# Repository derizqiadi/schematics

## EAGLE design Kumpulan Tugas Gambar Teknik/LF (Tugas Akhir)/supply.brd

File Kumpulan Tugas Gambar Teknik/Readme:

Hello!
My name is Derizqiadi Thoriq, student of Yogyakarta State University Gunung Kidul campus.
My NIM is 21507224030 and from GK1 class.

This repository was created to place the assignments that i was made while i was studying in the "Gambar Teknik" course in Semester 1.
This repository including :

1. Schematics assignment where i compile the components in the eagle application in schematic (.sch) form.
2. KMMI assignment where i arrange components in "board" (.brd) form and connect between components so that they can be used.
3. LF (Tugas Akhir) assignment where i arrange the components that have been provided. After that i connected the components on the coard (.brd) file, so that the components can be used.
4. Tugas Komponen, where i put the task that has been given previously ( tugas komponen, dan tugas adc_with_LDR).

Thank you for viewing my github repository page, i hope that what i upload on this page can be useful for other people, and i also hope to add more files to my repository and increase my skill in "Gambar Teknik" course.

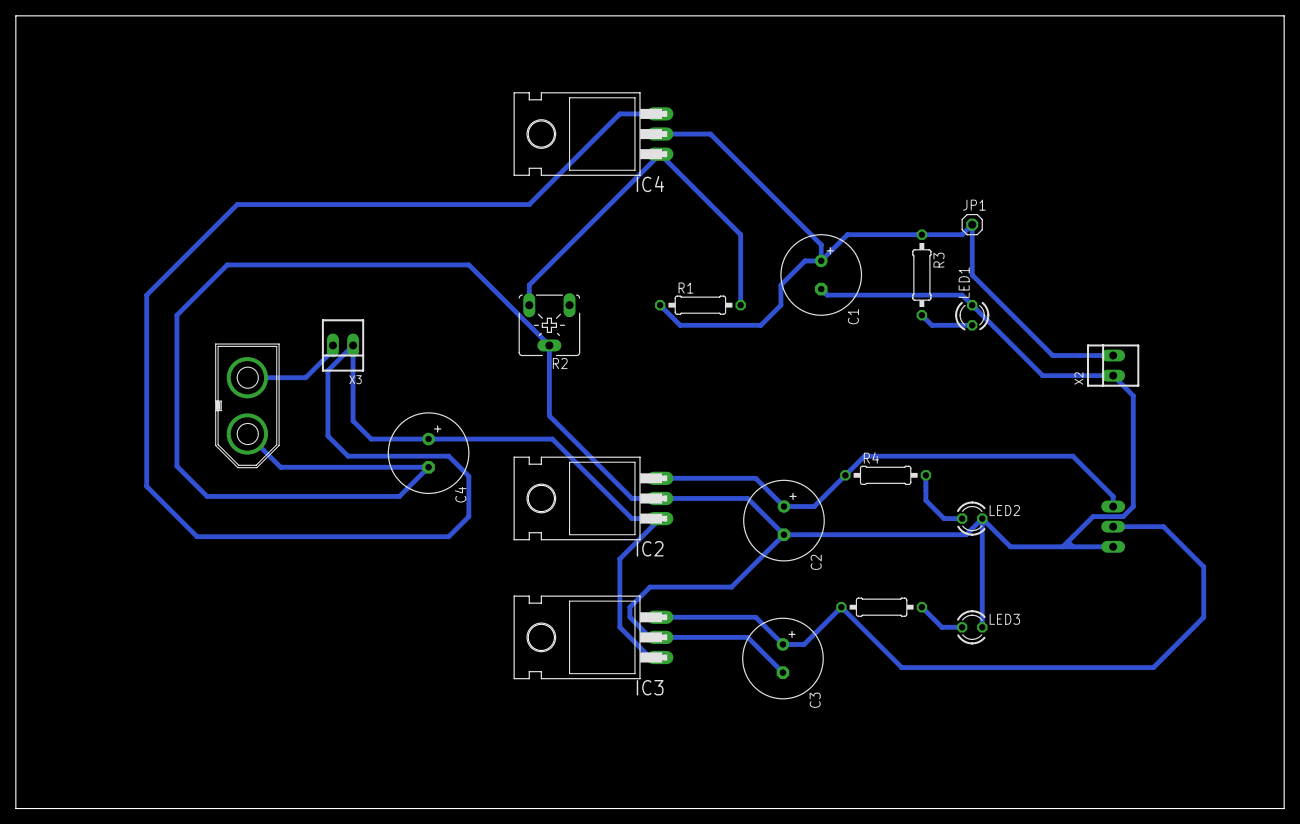
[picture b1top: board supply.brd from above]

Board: 2 copper layers, 160.0 x 100.0 mm, 20 parts (1 on the bottom side), 10 nets.

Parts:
C1, C2, C3, C4: 1000uF/16V; E3,5-10
IC2, IC3: 7805T; TO220H
IC4: 317T; TO220H
JP1: 1X01
LED1, LED2, LED3: LED3MM
R1: 1K2; 0207/10
R2: 20K; CA6V
R3, R4, R5: 1K; 0207/10
VIN: CON-XT60M
X1: VSYS; 22-23-2031
X2: VMOT; 22-23-2021
X3: switch; 22-23-2021

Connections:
+12V: C3.+, IC3.3, R5.1, X1.2
GND: C1.-, C2.-, C3.-, C4.-, IC2.2, IC3.2, LED1.K, LED2.K, LED3.K, R2.S, VIN.V-, X1.3, X2.1
unnamed: IC4.1, R1.2, R2.E
unnamed: LED1.A, R3.2
unnamed: LED3.A, R5.2
unnamed: VIN.V+, X3.2
unnamed: LED2.A, R4.2
VCC: C2.+, IC2.3, R4.1, X1.1
VDD: C1.+, IC4.2, JP1.1, R1.1, R3.1, X2.2
VPP: C4.+, IC2.1, IC3.1, IC4.3, X3.1

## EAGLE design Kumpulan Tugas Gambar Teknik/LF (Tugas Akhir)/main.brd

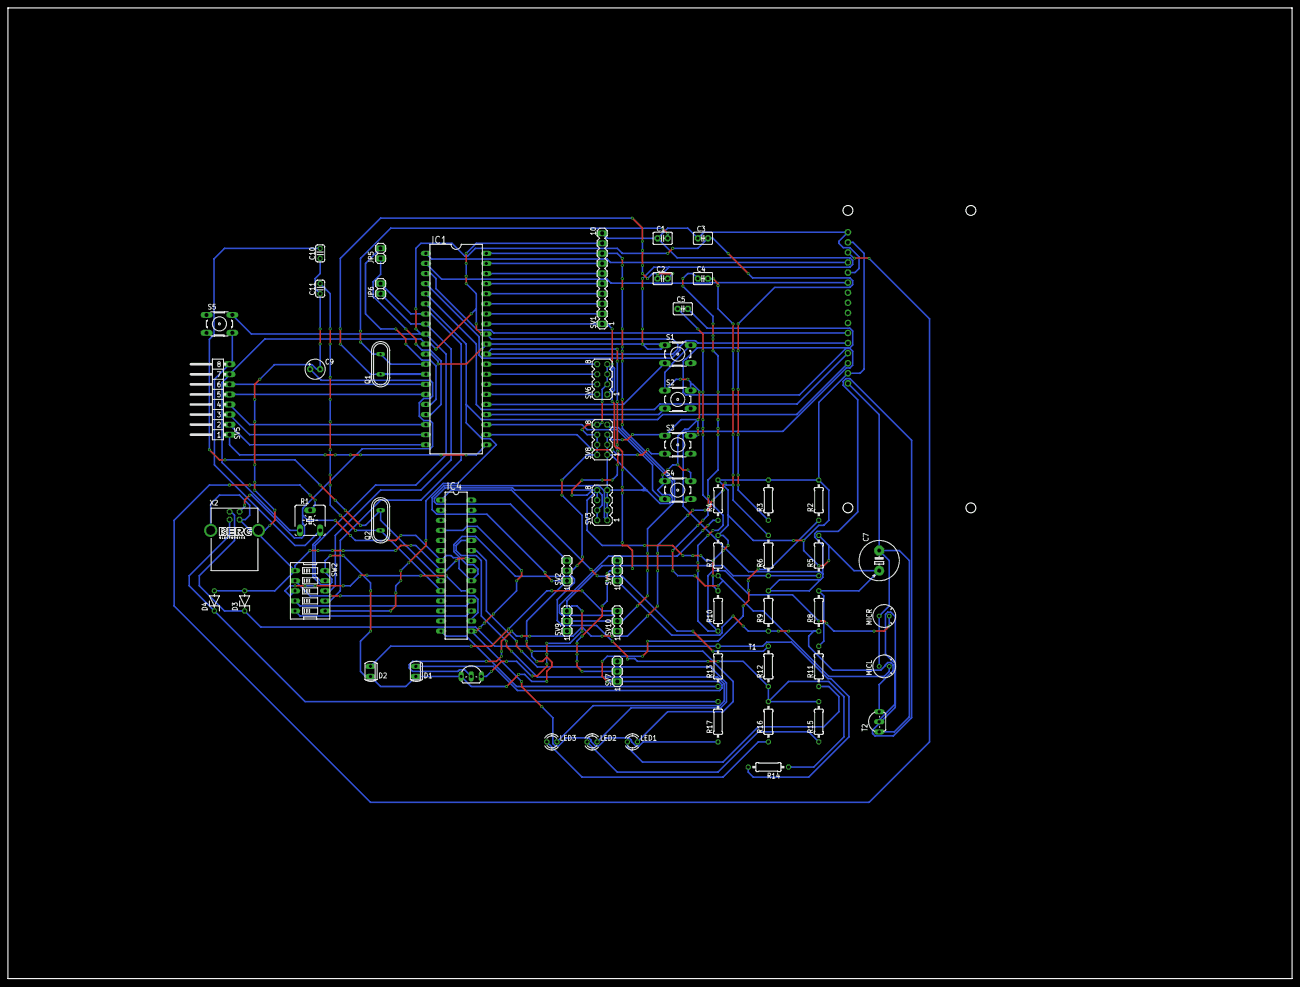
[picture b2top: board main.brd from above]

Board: 2 copper layers, 323.8 x 244.8 mm, 61 parts (1 on the bottom side), 65 nets.

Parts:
C1, C2: 22p; C2.5-3
C3: 10nF; C2.5-3
C4, C5: 100nF; C2.5-3
C7: 1000uF/16V; E5-10,5
C9: 10uF/16V; E2,5-5
C10, C11: 22pF; C025-024X044
D1, D2: SFH225
D3, D4: DZ3,6V; ZDIO-5
DIS1: TUXGR_16X2_R2
IC1: MEGA16-P; DIL40
IC4: MEGA8-P; DIL28-3
JP5, JP6: 1X02
LED1: merah; LED3MM
LED2: Merah; LED3MM
LED3: hijau; LED3MM
MICL: MC; F6050AP
MICR: MC; F6050AP
Q1: 8MHz; QS
Q2: 12MHz; QS
R1: 20K; CA6V
R2, R4: 56K; 0207/10
R3, R5, R7, R8, R10, R12: 10K; 0207/10
R6, R9: 100K; 0207/10
R11, R15, R16: 330; 0207/10
R13, R17: 68; 0207/10
R14: 2K2; 0207/10
S1, S2, S3, S4, S5: B3F-10XX
SV1: MA10-1
SV2, SV4, SV7, SV9, SV10: MA03-1
SV3, SV6, SV8: MA04-2
SV5: MA08-1W
SW2: EDG-05
T1, T2: TO92-EBC
X2: PN61729-S

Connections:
DGND: C9.-, C10.1, C11.1, D3.A, D4.A, IC4.8, IC4.22, SW2.1, X2.4, X2.S1, X2.S2
GND: C1.1, C2.1, C3.1, C7.-, D1.K, D2.K, DIS1.1, DIS1.5, DIS1.16, IC1.11, IC1.31, LED1.K, MICL.1, MICR.1, R1.E, S1.1, S1.2, S2.1, S2.2, S3.1, S3.2, S4.1, S4.2, S5.3, S5.4, SV1.10, SV2.1, SV3.1, SV3.3, SV3.5, SV3.7, SV5.8, SV8.1, SV8.3, SV8.5, SV8.7, SW2.10, T1.E, T2.E
MISO: IC1.7, JP6.2, SW2.7
MOSI: DIS1.14, IC1.6, SW2.6
unnamed: IC1.33, SV1.1, SV4.2, SV7.2
unnamed: IC1.34, SV1.2
unnamed: IC1.35, SV1.3
unnamed: IC1.36, SV1.4
unnamed: IC1.37, SV1.5
unnamed: IC1.38, SV1.6
unnamed: IC1.39, SV1.7
unnamed: D2.A, R4.1, SV10.3
unnamed: IC1.24, S2.3, S2.4
unnamed: DIS1.13, IC1.5
unnamed: DIS1.12, IC1.4
unnamed: DIS1.11, IC1.3
unnamed: DIS1.6, IC1.2
unnamed: R5.1, R6.1, SV9.3, T1.C
unnamed: DIS1.3, R1.S
unnamed: C1.2, IC1.12, Q1.2
unnamed: C2.2, IC1.13, Q1.1
unnamed: DIS1.4, IC1.1
unnamed: D1.A, R2.1, SV7.1
unnamed: IC1.23, S4.3, S4.4
unnamed: IC1.40, SV1.8, SV9.2, SV10.2
unnamed: C4.2, R6.2, T1.B
unnamed: C4.1, MICL.2, R7.1
unnamed: R8.1, R9.1, SV4.1, T2.C
unnamed: C5.2, R9.2, T2.B
unnamed: C5.1, MICR.2, R10.1
unnamed: IC1.22, S3.3, S3.4
unnamed: IC1.25, S1.3, S1.4
unnamed: IC1.21, SV5.1
unnamed: IC1.20, SV5.2
unnamed: IC1.19, SV5.3
unnamed: IC1.18, SV5.4
unnamed: IC1.15, SV5.5
unnamed: IC1.14, SV5.6
unnamed: IC1.16, JP5.2
unnamed: IC1.17, JP5.1
unnamed: LED1.A, R11.1
unnamed: IC4.1, R12.2
unnamed: IC1.26, SV6.2
unnamed: IC1.27, SV6.4
unnamed: IC1.28, SV6.6
unnamed: IC1.29, SV6.8
unnamed: C10.2, IC4.9, Q2.2
unnamed: C11.2, IC4.10, Q2.1
unnamed: IC4.14, R13.1
unnamed: LED2.A, R15.1
unnamed: LED3.A, R16.1
unnamed: IC4.23, LED2.K
unnamed: IC4.24, LED3.K
unnamed: D4.C, R17.2, X2.3
unnamed: IC4.4, IC4.15, R17.1
unnamed: D3.C, R13.2, R14.2, X2.2
unnamed: IC4.17, SW2.5
unnamed: IC4.18, SW2.4
unnamed: IC4.19, SW2.3
unnamed: IC4.16, SW2.2
RESET: C3.2, IC1.9, R3.1, S5.1, S5.2, SW2.9
SCK: IC1.8, JP6.1, SW2.8
VCC: C7.+, DIS1.2, DIS1.15, IC1.10, IC1.30, IC1.32, R1.A, R2.2, R3.2, R4.2, R5.2, R7.2, R8.2, R10.2, R11.2, SV1.9, SV2.3, SV3.2, SV3.4, SV3.6, SV3.8, SV5.7
VDD: SV2.2, SV6.1, SV6.3, SV6.5, SV6.7, SV8.2, SV8.4, SV8.6, SV8.8
VPP: C9.+, IC4.7, IC4.20, R12.1, R14.1, R15.2, R16.2, X2.1

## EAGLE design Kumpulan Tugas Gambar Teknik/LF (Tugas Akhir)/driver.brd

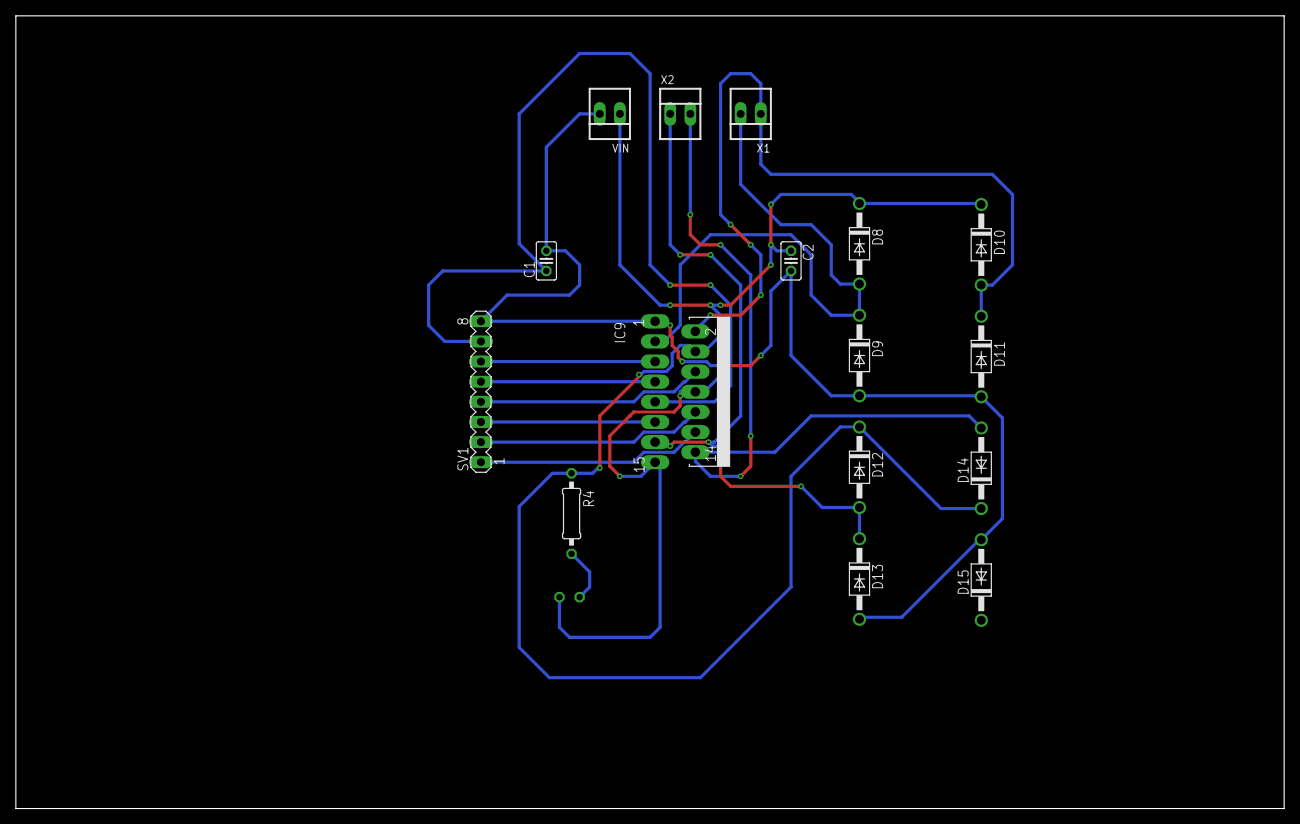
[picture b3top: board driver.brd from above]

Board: 2 copper layers, 160.0 x 100.0 mm, 17 parts (1 on the bottom side), 14 nets.

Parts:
C1, C2: 100nF; C025-025X050
D8, D9, D10, D11, D12, D13, D14, D15: 1N4004; DO41-10
IC9: L298; MULTIWATT-15
LED1: LED3MM
R4: 330; 0207/10
SV1: MA08-1
VIN: 22-23-2021
X1, X2: 22-23-2021

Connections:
GND: C1.2, C2.2, D9.A, D11.A, D13.A, D15.A, IC9.1, IC9.8, IC9.15, LED1.K, SV1.8, VIN.2
unnamed: IC9.5, SV1.6
unnamed: IC9.7, SV1.5
unnamed: IC9.12, SV1.1
unnamed: IC9.10, SV1.2
unnamed: IC9.6, SV1.4
unnamed: IC9.11, SV1.3
unnamed: LED1.A, R4.2
unnamed: D8.A, D9.C, IC9.3, X1.2
unnamed: D10.A, D11.C, IC9.2, X1.1
unnamed: D12.A, D13.C, IC9.13, X2.1
unnamed: D14.A, D15.C, IC9.14, X2.2
VCC: C1.1, IC9.9, SV1.7
VDD: C2.1, D8.C, D10.C, D12.C, D14.C, IC9.4, R4.1, VIN.1

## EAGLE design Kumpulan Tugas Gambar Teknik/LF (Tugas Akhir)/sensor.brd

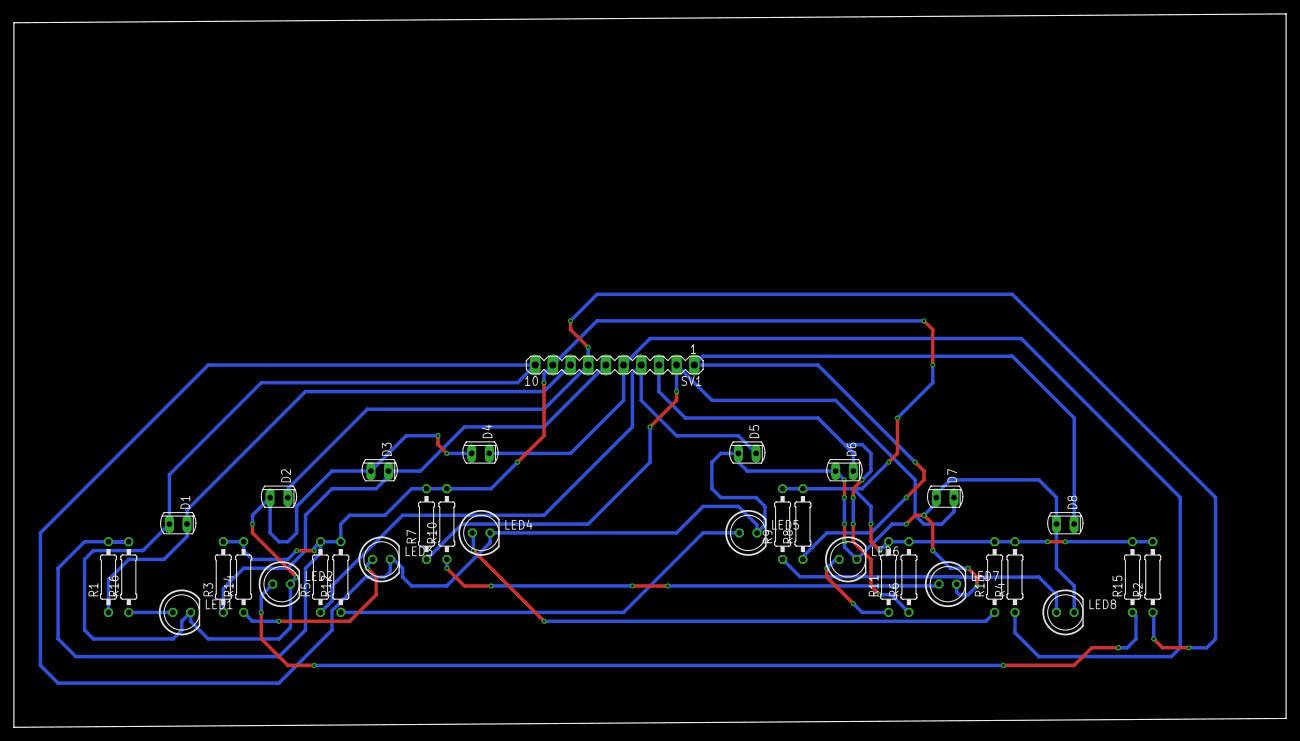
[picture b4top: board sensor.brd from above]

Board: 2 copper layers, 182.9 x 102.5 mm, 33 parts (0 on the bottom side), 18 nets.

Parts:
D1, D2, D3, D4, D5, D6, D7, D8: PhotoDioda; SFH225
LED1, LED2, LED3, LED4, LED5, LED6, LED7, LED8: LED putih SB; LED5MM
R1, R2, R3, R4, R5, R6, R7, R8: 0207/10
R9, R10, R11, R12, R13, R14, R15, R16: 330; 0207/10
SV1: MA10-1

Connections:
GND: D1.A, D2.A, D3.A, D4.A, D5.A, D6.A, D7.A, D8.A, LED1.K, LED2.K, LED3.K, LED4.K, LED5.K, LED6.K, LED7.K, LED8.K, SV1.10
unnamed: LED7.A, R10.1
unnamed: D7.K, R7.1, SV1.2
unnamed: D8.K, R8.1, SV1.1
unnamed: D1.K, R1.1, SV1.8
unnamed: D2.K, R2.1, SV1.7
unnamed: D3.K, R3.1, SV1.6
unnamed: D5.K, R5.1, SV1.4
unnamed: D4.K, R4.1, SV1.5
unnamed: D6.K, R6.1, SV1.3
unnamed: LED6.A, R11.1
unnamed: LED5.A, R12.1
unnamed: LED4.A, R13.1
unnamed: LED3.A, R14.1
unnamed: LED2.A, R15.1
unnamed: LED1.A, R16.1
unnamed: LED8.A, R9.1
VCC: R1.2, R2.2, R3.2, R4.2, R5.2, R6.2, R7.2, R8.2, R9.2, R10.2, R11.2, R12.2, R13.2, R14.2, R15.2, R16.2, SV1.9

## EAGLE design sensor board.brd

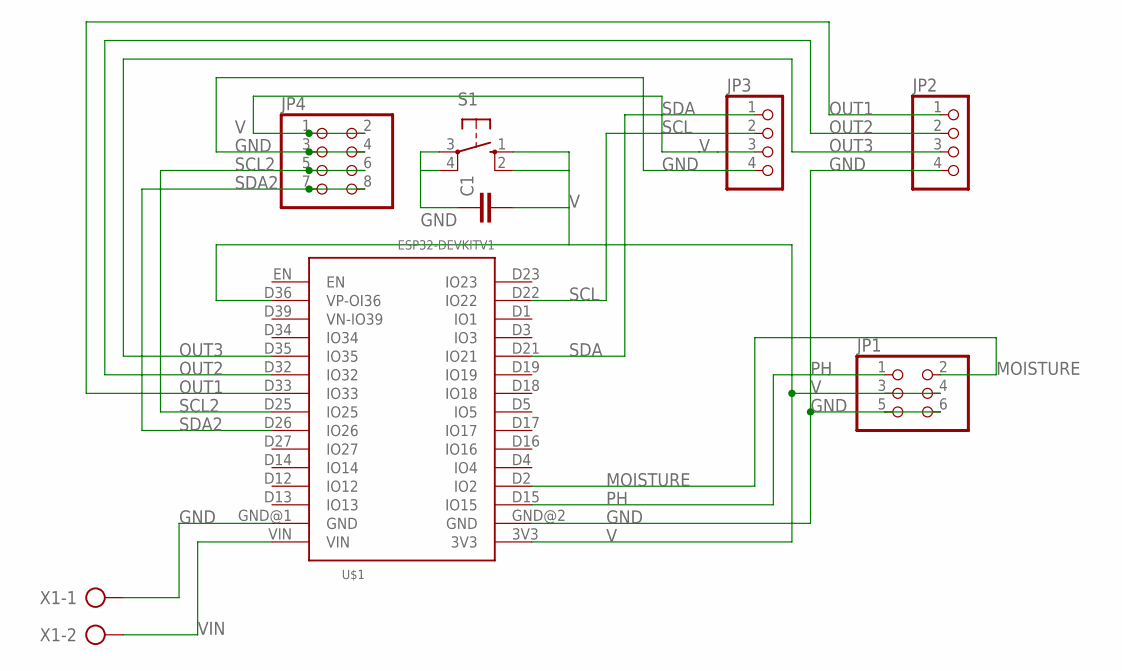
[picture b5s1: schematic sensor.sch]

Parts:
C1: C-EU050-030X075; C050-030X075
JP1: PINHD-2X3; 2X03
JP2, JP3: PINHD-1X4; 1X04
JP4: PINHD-2X4; 2X04
S1: 10-XX; B3F-10XX
U$1: ESP32DEVKITV1; ESP32-DEVKITV1
X1: AK300/2

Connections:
GND: C1.1, JP1.5, JP1.6, JP2.4, JP3.4, JP4.3, JP4.4, S1.3, S1.4 (P1), U$1.GND@1 (GND), U$1.GND@2 (GND), X1.1
MOISTURE: JP1.2, U$1.D2 (IO2)
OUT1: JP2.1, U$1.D33 (IO33)
OUT2: JP2.2, U$1.D32 (IO32)
OUT3: JP2.3, U$1.D35 (IO35)
PH: JP1.1, U$1.D15 (IO15)
SCL: JP3.2, U$1.D22 (IO22)
SCL2: JP4.5, JP4.6, U$1.D25 (IO25)
SDA: JP3.1, U$1.D21 (IO21)
SDA2: JP4.7, JP4.8, U$1.D26 (IO26)
V: C1.2, JP1.3, JP1.4, JP3.3, JP4.1, JP4.2, S1.1 (S), S1.2 (S1), U$1.3V3, U$1.D36 (VP-OI36)
VIN: U$1.VIN, X1.2

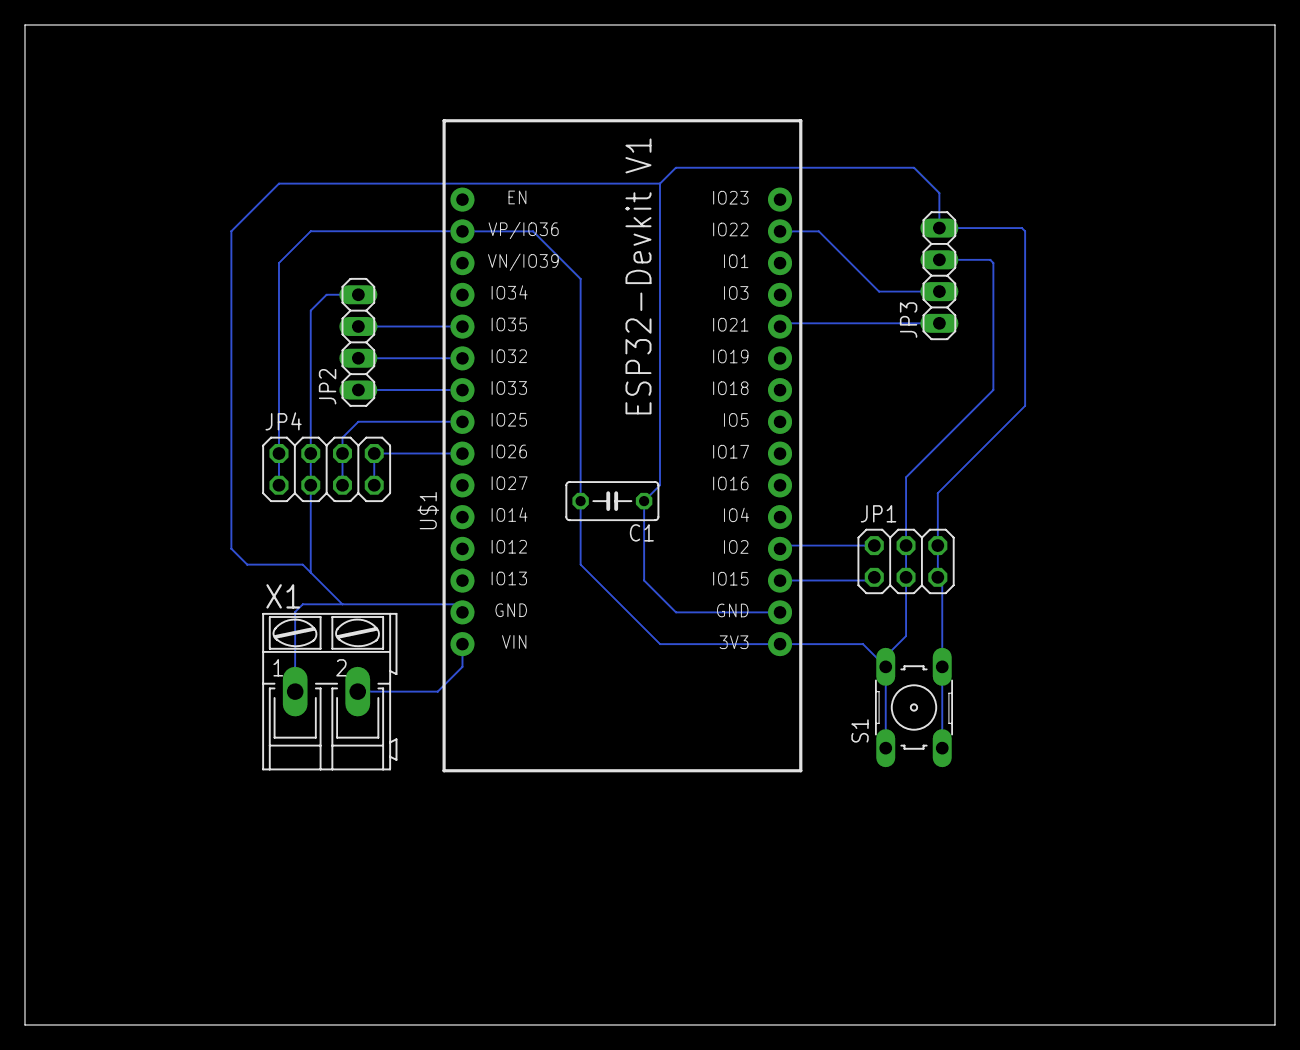
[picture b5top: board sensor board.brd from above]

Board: 2 copper layers, 100.0 x 80.0 mm, 8 parts (0 on the bottom side), 12 nets.

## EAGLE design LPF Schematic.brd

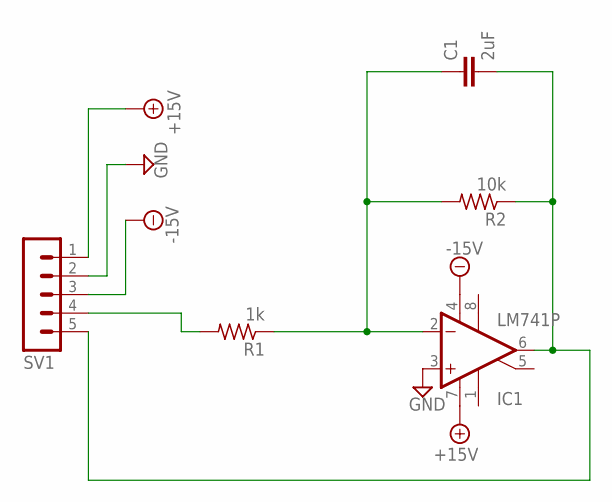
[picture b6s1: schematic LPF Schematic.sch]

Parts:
C1: 2uF; C0603
IC1: LM741P; DIL08
R1: 1k; R0603
R2: 10k; R0603
SV1: MA05-1

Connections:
+15V: IC1.7 (V+), SV1.1
-15V: IC1.4 (V-), SV1.3
GND: IC1.3 (+IN), SV1.2
unnamed: C1.1, IC1.2 (-IN), R1.1, R2.2
unnamed: R1.2, SV1.4
unnamed: C1.2, IC1.6 (OUT), R2.1, SV1.5

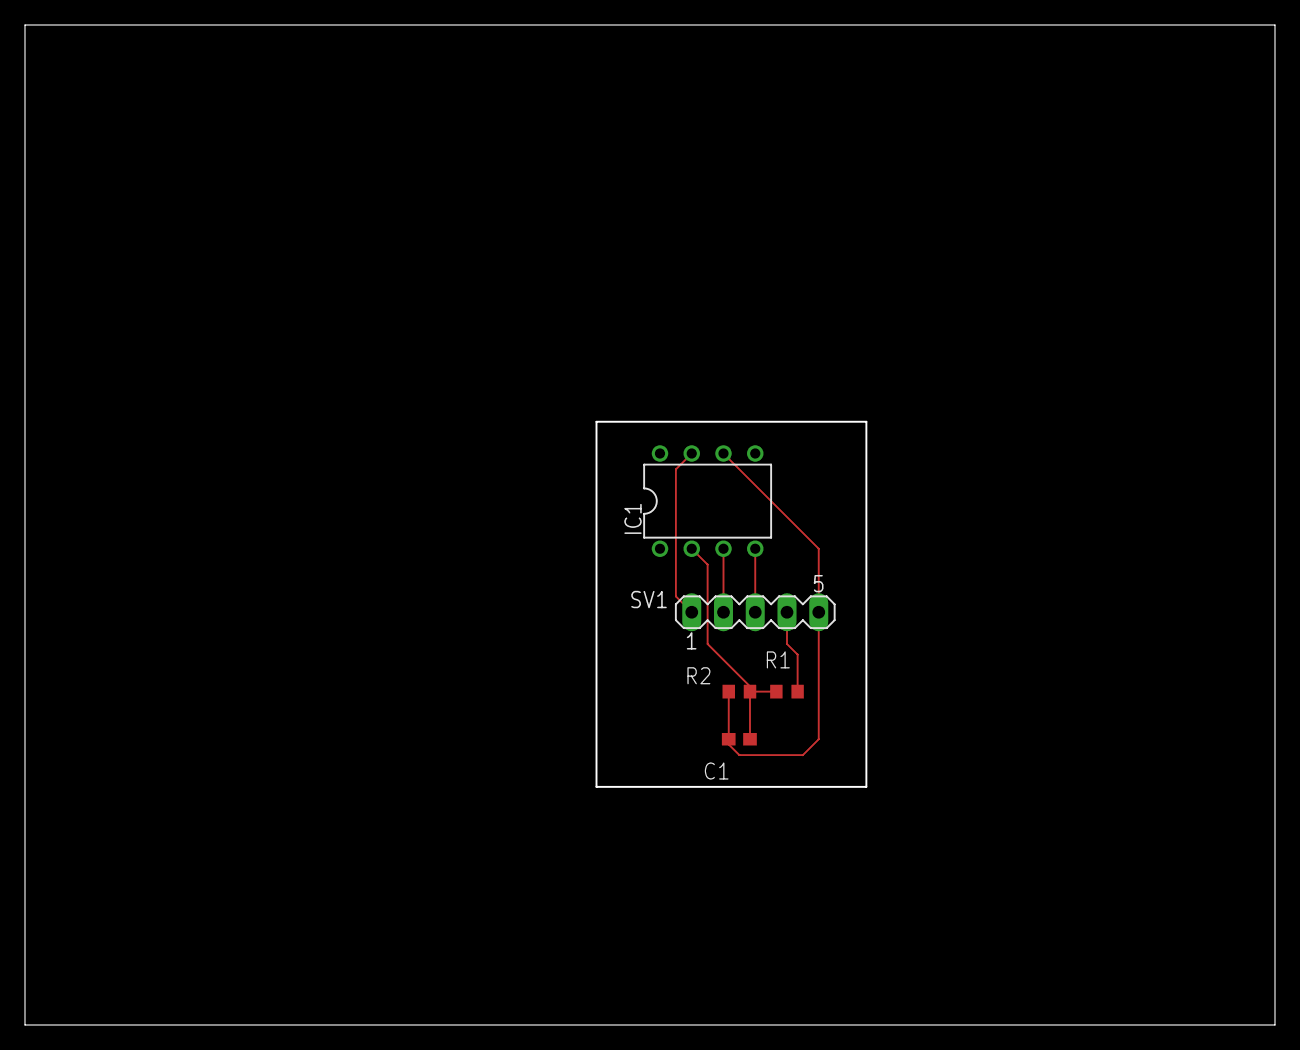
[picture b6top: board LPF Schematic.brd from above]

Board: 2 copper layers, 100.0 x 80.0 mm, 5 parts (0 on the bottom side), 6 nets.

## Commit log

2021-11-18 Create LF
2021-11-18 Rename LF to test
2021-12-26 Create Kumpulan Tugas Gambar Teknik
2021-12-26 Create index.Kumpulan Tugas Gambar Teknik
2021-12-26 Create test
2021-12-26 Rename test to Readme
